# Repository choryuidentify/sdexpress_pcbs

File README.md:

# microSD Express PCBs

This repository contains several PCB designs for adapters related to microSD
Express cards.

- [M.2-M card to microSD Express socket](m2_m_card-to-usdex_socket/README.md)
- [microSD Express card to FPC](usdex_card-to-fpc/README.md)
- [fpc](fpc/README.md)
- [FPC to M.2-M socket](fpc-to-m2_m_socket/README.md)
- [microSD Express card to M.2-M socket](usdex-to-m2_m_socket/README.md)

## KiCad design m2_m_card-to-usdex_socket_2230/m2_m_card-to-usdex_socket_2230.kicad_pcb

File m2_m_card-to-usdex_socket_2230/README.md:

# M.2-M card to microSD Express socket

This allows connecting a microSD Express card directly to an M.2 Key M slot, so
you can use it as a PCIe NVME device.

See
[my blog post](https://mzimmermann.info/posts/a-microsd-express-card-in-an-m2-slot/)
for more information.

JLCPCB order parameters:

- **Gerber file**: gerbers_Y3
- **Build Time**: 5-6 days
- **Base Material**: FR-4
- **Layers**: 6
- **Dimension**: 22 mm * 80 mm
- **PCB Qty**: 5
- **Product Type**: Industrial/Consumer electronics
- **Different Design**: 1
- **Delivery Format**: Single PCB
- **PCB Thickness**: 0.8mm
- **Specify Stackup**: yes JLC06081H-2116
- **Impedance Control**: No requirement
- **PCB Color**: Green
- **Silkscreen**: White
- **Material Type**: FR-4 TG155
- **Via Covering**: Epoxy Filled & Capped
- **Surface Finish**: ENIG
- **Gold Fingers**: 2U"
- **Deburring/Edge rounding**: Yes
- **Outer Copper Weight**: 1 oz
- **Inner Copper Weight**: 0.5 oz
- **Gold Fingers**: Yes
- **Beveling**: No
- **Electrical Test**: Flying Probe Fully Test
- **Castellated Holes**: no
- **Press-Fit Hole**: No
- **Edge Plating**: No
- **Mark on PCB**: Remove Mark
- **Blind Slot**: No
- **Min via hole size/diameter**: 0.3mm/(0.4/0.45mm)
- **4-Wire Kelvin Test**: Yes
- **Paper between PCBs**: No
- **Appearance Quality**: IPC Class 2 Standard
- **Confirm Production file**: No
- **Silkscreen Technology**: Ink-jet/Screen Printing Silkscreen
- **Package Box**: With JLCPCB logo
- **Inspection Report**: No
- **Board Outline Tolerance**: ±0.2mm(Regular)

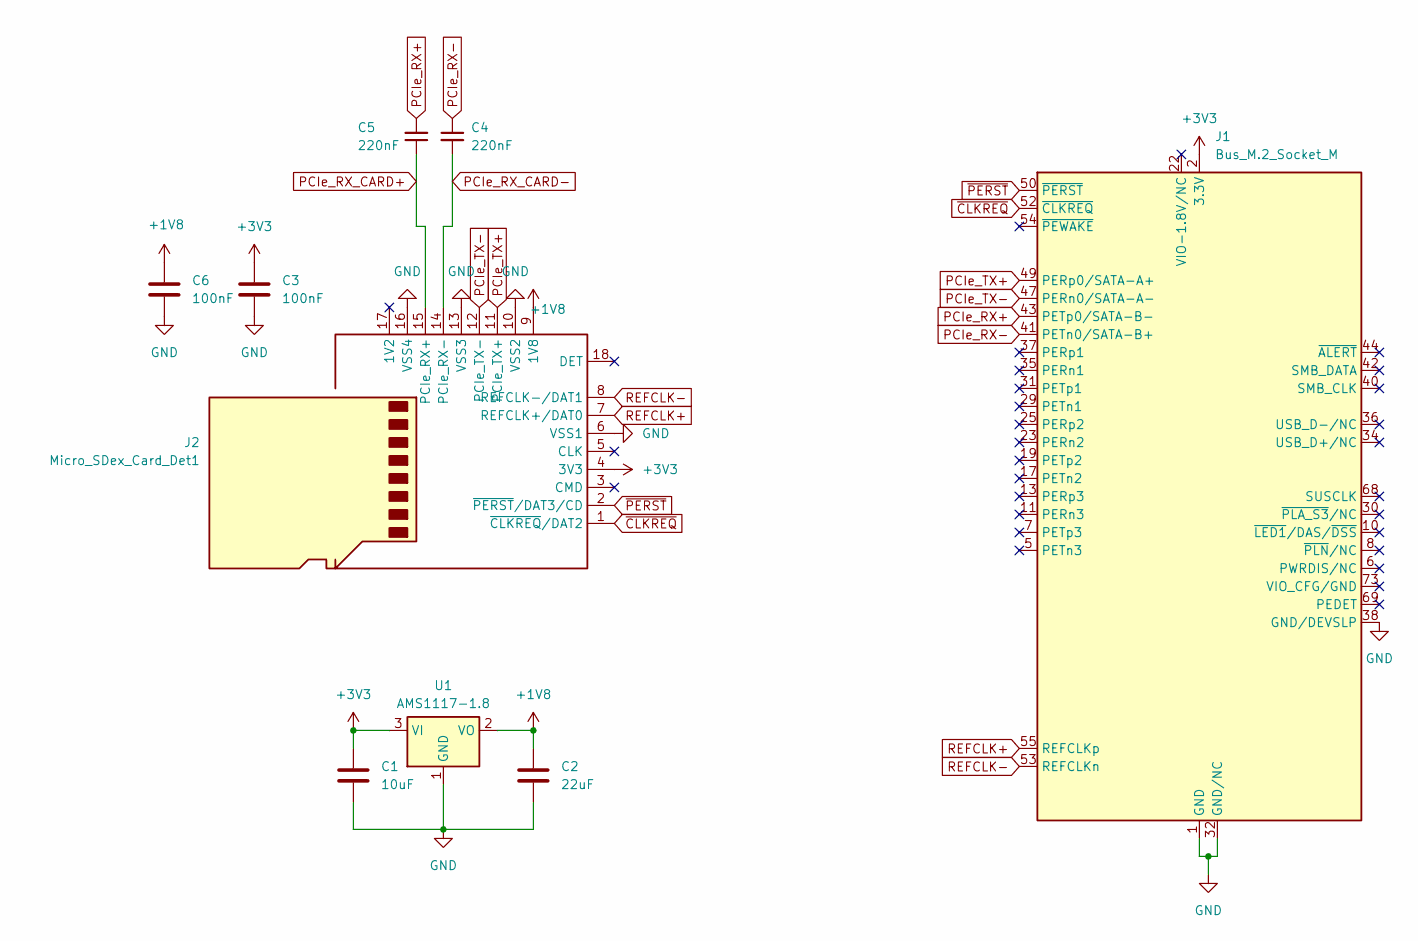
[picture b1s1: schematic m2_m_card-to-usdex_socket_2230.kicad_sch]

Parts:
C1: 10uF; C_0603_1608Metric
C2: 22uF; C_0603_1608Metric
C3, C6: 100nF; C_0603_1608Metric
C4, C5: 220nF; C_0603_1608Metric
J1: Bus_M.2_Socket_M; 2230-key-M
J2: Micro_SDex_Card_Det1; Amphenol 10102166A812A
U1: AMS1117-1.8; SOT-223-3_TabPin2

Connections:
+1V8: C2.1, C6.1, J2.9 (1V8), U1.2 (VO)
+3V3: C1.1, C3.1, J1.2 (3.3V), J1.4 (3.3V), J1.12 (3.3V), J1.14 (3.3V), J1.16 (3.3V), J1.18 (3.3V), J1.70 (3.3V), J1.72 (3.3V), J1.74 (3.3V), J2.4 (3V3), U1.3 (VI)
GND: C1.2, C2.2, C3.2, C6.2, J1.1 (GND), J1.3 (GND), J1.9 (GND), J1.15 (GND), J1.21 (GND), J1.27 (GND), J1.32 (GND/NC), J1.33 (GND), J1.38 (GND/DEVSLP), J1.39 (GND), J1.45 (GND), J1.51 (GND), J1.57 (GND), J1.71 (GND), J1.75 (GND), J1.76 (GND), J1.77 (GND), J2.6 (VSS1), J2.10 (VSS2), J2.13 (VSS3), J2.16 (VSS4), U1.1 (GND)
PCIe_RX+: C5.2, J1.43 (PETp0/SATA-B-)
PCIe_RX-: C4.1, J1.41 (PETn0/SATA-B+)
PCIe_RX_CARD+: C5.1, J2.15 (PCIe_RX+)
PCIe_RX_CARD-: C4.2, J2.14 (PCIe_RX-)
PCIe_TX+: J1.49 (PERp0/SATA-A+), J2.11 (PCIe_TX+)
PCIe_TX-: J1.47 (PERn0/SATA-A-), J2.12 (PCIe_TX-)
REFCLK+: J1.55 (REFCLKp), J2.7 (REFCLK+/DAT0)
REFCLK-: J1.53 (REFCLKn), J2.8 (REFCLK-/DAT1)
~CLKREQ: J1.52 (~CLKREQ), J2.1 (~CLKREQ/DAT2)
~PERST: J1.50 (~PERST), J2.2 (~PERST/DAT3/CD)

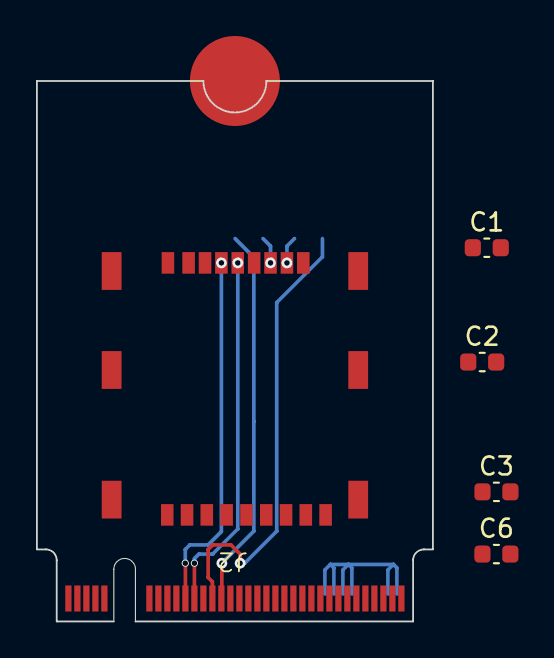
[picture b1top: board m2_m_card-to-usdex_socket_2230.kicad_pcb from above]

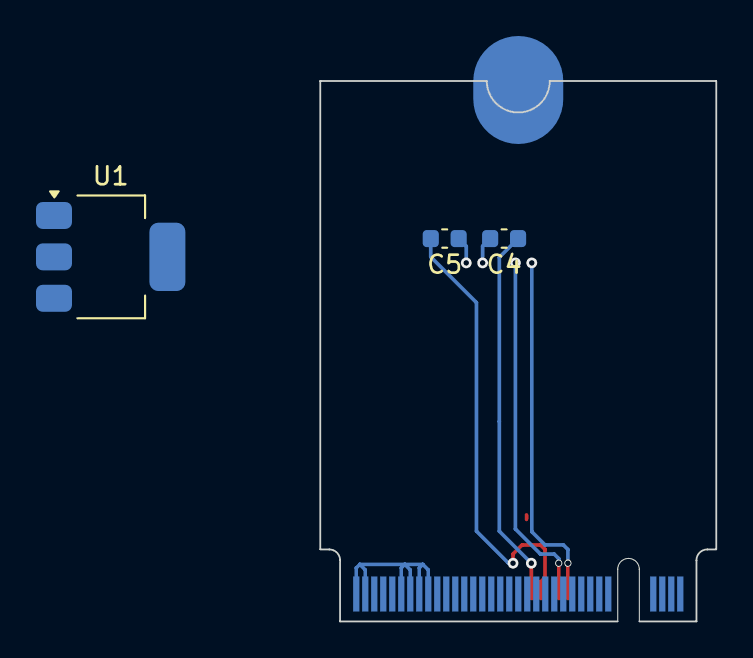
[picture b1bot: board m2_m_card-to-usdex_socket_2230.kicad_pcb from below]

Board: 2 copper layers, 22.0 x 30.0 mm, 9 parts (3 on the bottom side), 13 nets.

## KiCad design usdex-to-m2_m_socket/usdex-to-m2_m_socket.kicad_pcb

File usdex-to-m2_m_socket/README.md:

# microSD Express card to M.2-M socket

Connects an M.2 Key-M SSD to a microSD Express slot.

JLCPCB order parameters:

- **Gerber file**: usdex-to-m2_m_socket_Y8
- **Build Time**: 3-4 days (PCBA Only)
- **Base Material**: FR-4
- **Layers**: 6
- **Dimension**: 4 mm* 54.42 mm
- **PCB Qty**: 5
- **Product Type**: Industrial/Consumer electronics
- **Different Design**: 1
- **Delivery Format**: Single PCB
- **PCB Thickness**: 0.8mm
- **Specify Stackup**: yes JLC06081H-2116
- **Impedance Control**: No requirement
- **PCB Color**: Green
- **Silkscreen**: White
- **Material Type**: FR-4 TG155
- **Via Covering**: Epoxy Filled & Capped
- **Surface Finish**: ENIG Gold Fingers: 2U"
- **Deburring/Edge rounding**: No
- **Outer Copper Weight**: 1 oz
- **Inner Copper Weight**: 0.5 oz
- **Gold Fingers**: Yes
- **Electrical Test**: Flying Probe Fully Test
- **Castellated Holes**: no
- **Press-Fit Hole**: No
- **Edge Plating**: No
- **Mark on PCB**: Remove Mark
- **Blind Slot**: No
- **Min via hole size/diameter**: 0.3mm/(0.4/0.45mm)
- **4-Wire Kelvin Test**: No
- **Paper between PCBs**: No
- **Appearance Quality**: IPC Class 2* Standard
- **Confirm Production file**: No
- **Silkscreen Technology**: Ink-jet/Screen Printing Silkscreen
- **Package Box**: With JLCPCB logo
- **Inspection Report**: No
- **Board Outline Tolerance**: ±0.2mm(Regular)

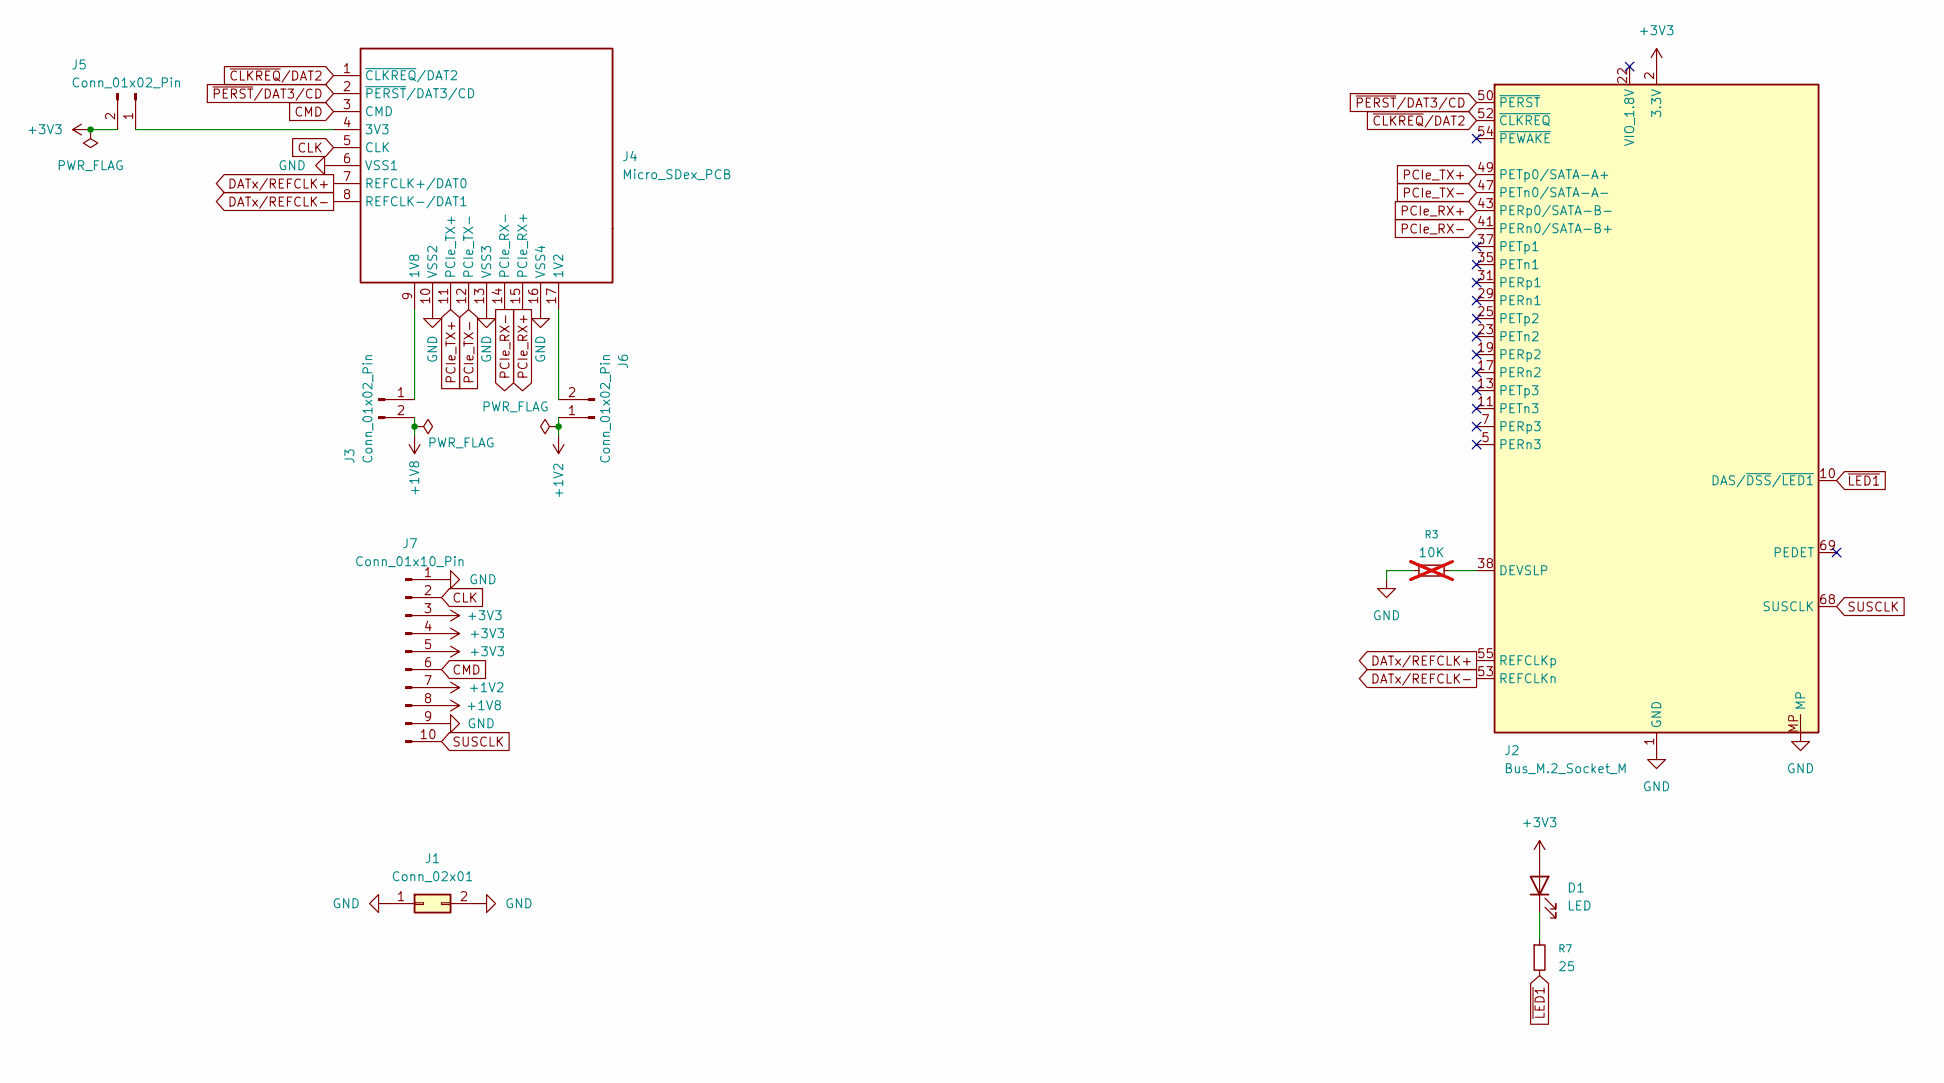
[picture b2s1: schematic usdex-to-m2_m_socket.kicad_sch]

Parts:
D1: LED; LED_0805_2012Metric; LCSC Part # C2297
J1: Conn_02x01; PinHeader_1x02_P2.54mm_Vertical
J2: Bus_M.2_Socket_M; CONN-SMD_APCI0146-P001A-nohole; LCSC Part # C841645
J3, J5, J6: Conn_01x02_Pin; PinHeader_1x02_P2.54mm_Vertical
J4: Micro_SDex_PCB; usdex-male-open_bottom
J7: Conn_01x10_Pin; PinHeader_1x10_P2.54mm_Vertical
R3: 10K; R_0402_1005Metric; not fitted
R7: 25; R_0805_2012Metric; LCSC Part # C17544

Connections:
+1V2: J6.1, J7.7
+1V8: J3.2, J7.8
+3V3: D1.2 (A), J2.2 (3.3V), J2.4 (3.3V), J2.12 (3.3V), J2.14 (3.3V), J2.16 (3.3V), J2.18 (3.3V), J2.70 (3.3V), J2.72 (3.3V), J2.74 (3.3V), J5.2, J7.3, J7.4, J7.5
CLK: J4.5 (CLK), J7.2
CMD: J4.3 (CMD), J7.6
DATx/REFCLK+: J2.55 (REFCLKp), J4.7 (REFCLK+/DAT0)
DATx/REFCLK-: J2.53 (REFCLKn), J4.8 (REFCLK-/DAT1)
GND: J1.1, J1.2, J2.1 (GND), J2.3 (GND), J2.9 (GND), J2.15 (GND), J2.21 (GND), J2.27 (GND), J2.33 (GND), J2.39 (GND), J2.45 (GND), J2.51 (GND), J2.57 (GND), J2.71 (GND), J2.73 (GND), J2.75 (GND), J2.MP, J4.6 (VSS1), J4.10 (VSS2), J4.13 (VSS3), J4.16 (VSS4), J7.1, J7.9, R3.1
unnamed: D1.1 (K), R7.1
unnamed: J2.38 (DEVSLP), R3.2
unnamed: J3.1, J4.9 (1V8)
unnamed: J4.17 (1V2), J6.2
unnamed: J4.4 (3V3), J5.1
PCIe_RX+: J2.43 (PERp0/SATA-B-), J4.15 (PCIe_RX+)
PCIe_RX-: J2.41 (PERn0/SATA-B+), J4.14 (PCIe_RX-)
PCIe_TX+: J2.49 (PETp0/SATA-A+), J4.11 (PCIe_TX+)
PCIe_TX-: J2.47 (PETn0/SATA-A-), J4.12 (PCIe_TX-)
SUSCLK: J2.68 (SUSCLK), J7.10
~CLKREQ/DAT2: J2.52 (~CLKREQ), J4.1 (~CLKREQ/DAT2)
~LED1: J2.10 (DAS/~DSS/~LED1), R7.2
~PERST/DAT3/CD: J2.50 (~PERST), J4.2 (~PERST/DAT3/CD)

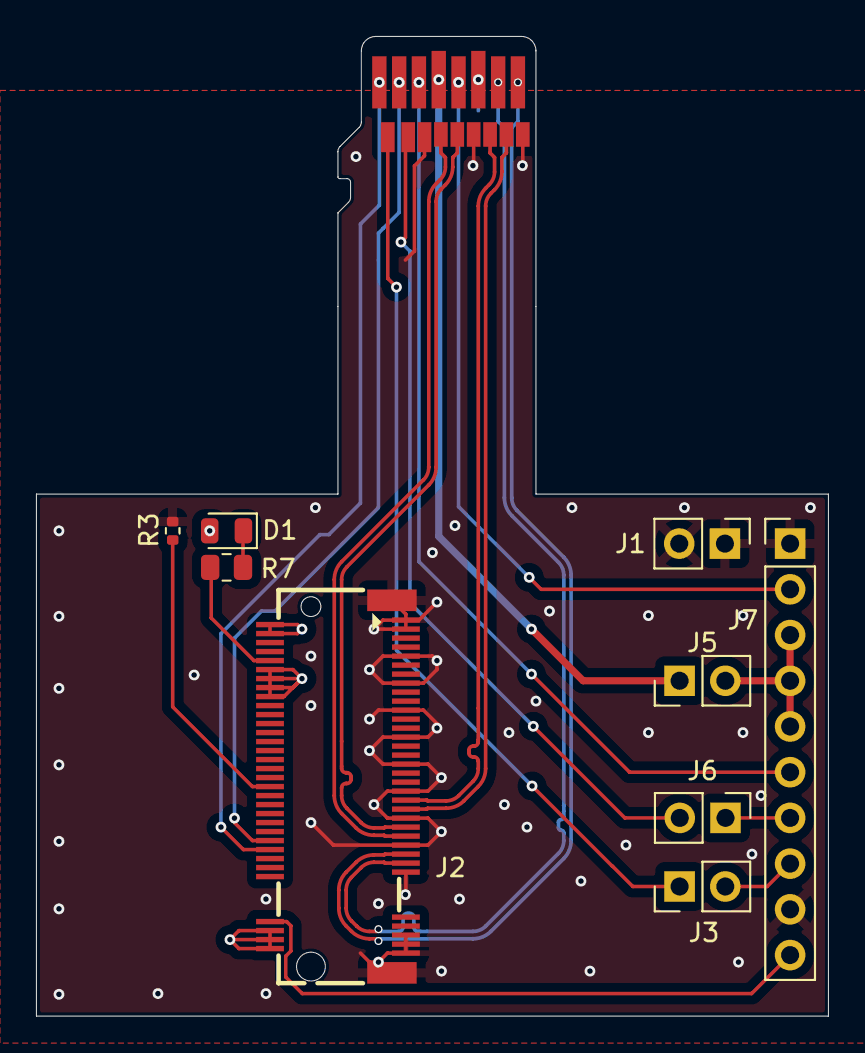
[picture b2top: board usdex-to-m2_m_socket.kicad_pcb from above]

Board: 6 copper layers, 44.0 x 54.4 mm, 10 parts (0 on the bottom side), 21 nets.

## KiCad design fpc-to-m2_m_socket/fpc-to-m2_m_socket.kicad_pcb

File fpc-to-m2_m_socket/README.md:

# FPC to M.2-M socket

> [!WARNING]
> This didn't work out due issues with properly soldering the FPC.

Connects an M.2 Key-M SSD to [FPC](../fpc/README.md).

JLCPCB order parameters:

- **Gerber file**: fpc-to-m2_m_socket_Y4
- **Build Time**: 3-4 days (PCBA Only)
- **Base Material**: FR-4
- **Layers**: 6
- **Dimension**: 99.3 mm* 70.58 mm
- **PCB Qty**: 5
- **Product Type**: Industrial/Consumer electronics
- **Different Design**: 1
- **Delivery Format**: Single PCB
- **PCB Thickness**: 0.8mm
- **Specify Stackup**: yes JLC06081H-2116
- **Impedance Control**: No requirement
- **PCB Color**: Green
- **Silkscreen**: White
- **Material Type**: FR-4 TG155
- **Via Covering**: Epoxy Filled & Capped
- **Surface Finish**: ENIG Gold Fingers: 2U"
- **Deburring/Edge rounding**: No
- **Outer Copper Weight**: 1 oz
- **Inner Copper Weight**: 0.5 oz
- **Gold Fingers**: No
- **Electrical Test**: Flying Probe Fully Test
- **Castellated Holes**: no
- **Press-Fit Hole**: No
- **Edge Plating**: No
- **Mark on PCB**: Remove Mark
- **Blind Slot**: No
- **Min via hole size/diameter**: 0.3mm/(0.4/0.45mm)
- **4-Wire Kelvin Test**: No
- **Paper between PCBs**: No
- **Appearance Quality**: IPC Class 2* Standard
- **Confirm Production file**: Yes
- **Silkscreen Technology**: Ink-jet/Screen Printing Silkscreen
- **Package Box**: With JLCPCB logo
- **Inspection Report**: No
- **Board Outline Tolerance**: ±0.2mm(Regular)

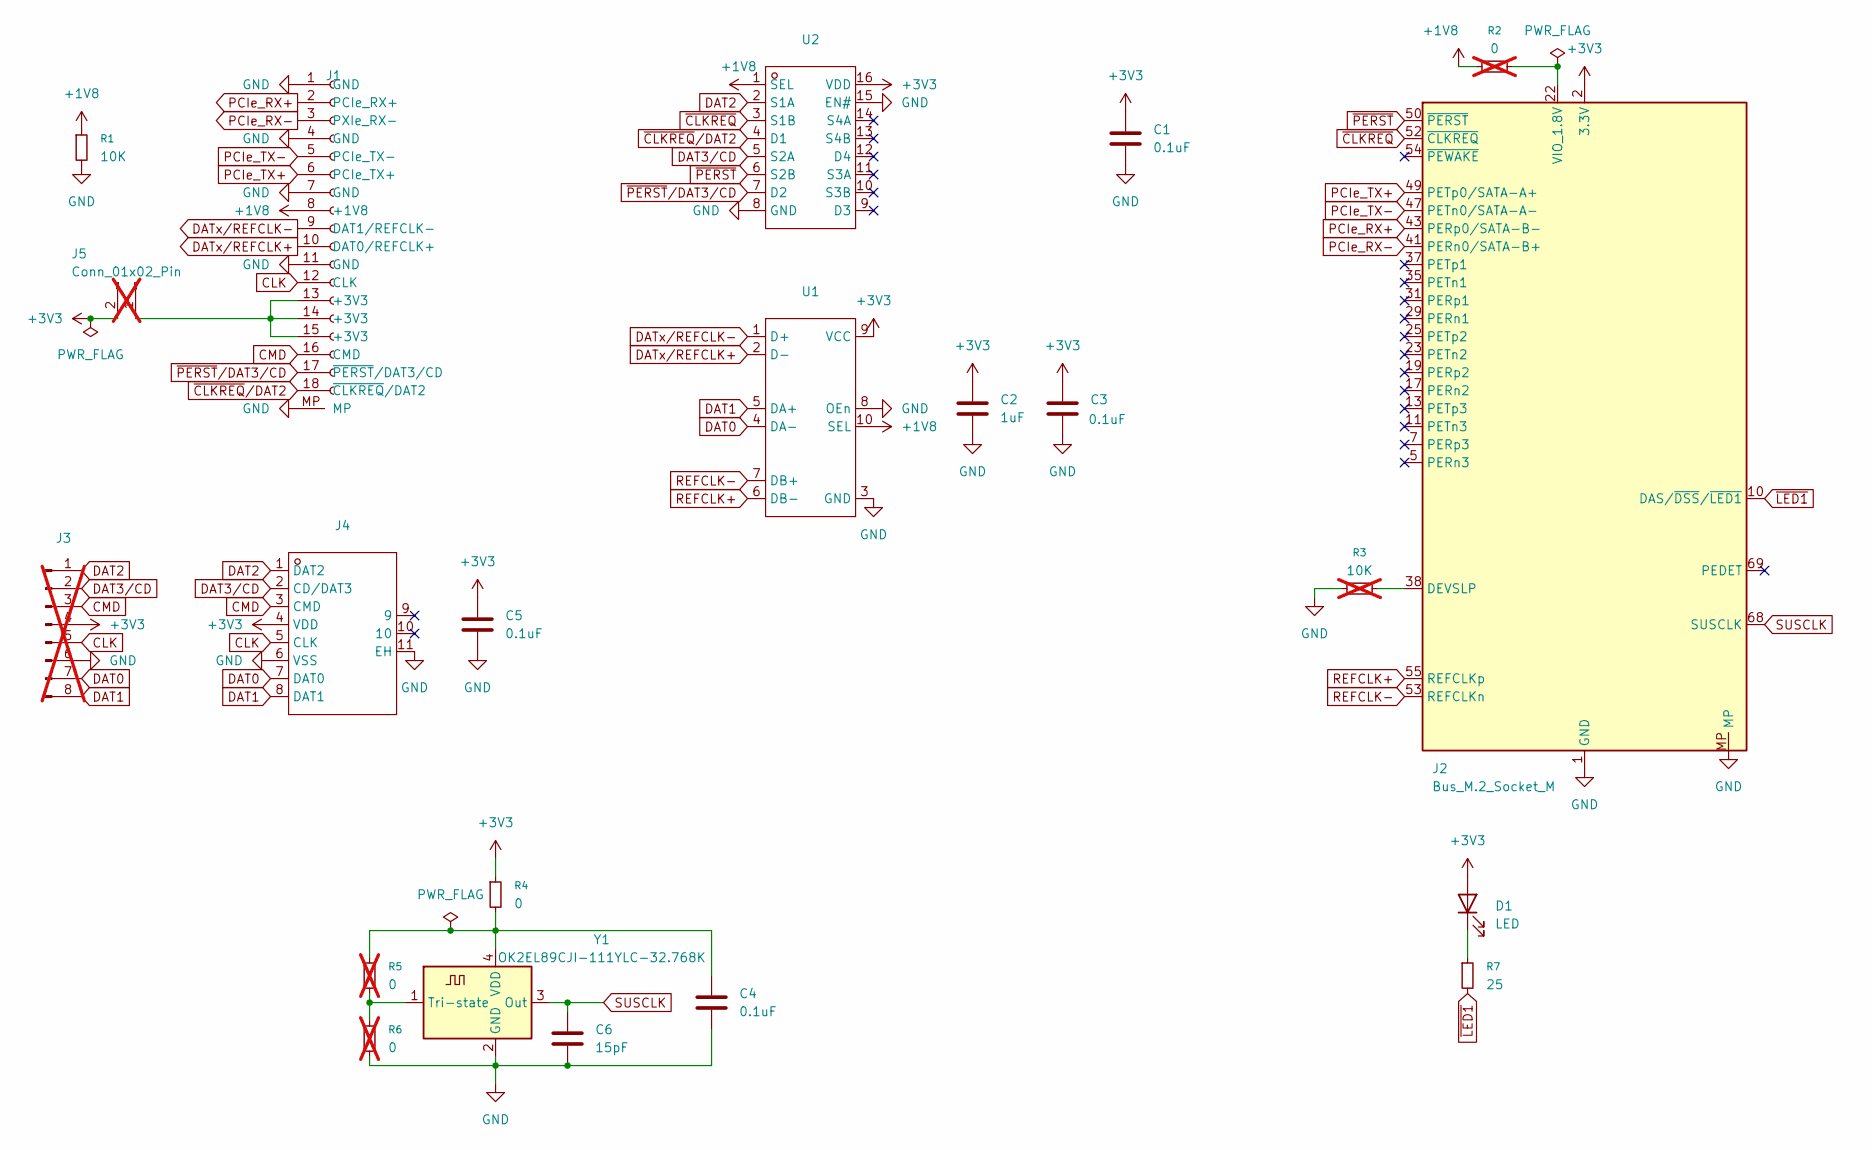
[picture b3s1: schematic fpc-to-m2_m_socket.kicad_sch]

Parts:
C1, C3, C4, C5: 0.1uF; C_0402_1005Metric; LCSC Part # C1525
C2: 1uF; C_0402_1005Metric; LCSC Part # C52923
C6: 15pF; C_0402_1005Metric; LCSC Part # C1548
D1: LED; LED_0805_2012Metric; LCSC Part # C2297
J1: FPC-SMD_18P-P1.00_JS_AFA07-S18XXX; LCSC Part # C262744
J2: Bus_M.2_Socket_M; CONN-SMD_APCI0146-P001A; LCSC Part # C841645
J3: PinHeader_1x08_P2.54mm_Vertical; not fitted
J4: TF-SMD_503398-1892; Manufacturer Part 5033981892; LCSC Part Name 自弹式 MicroSD卡(TF卡) 卡座
J5: Conn_01x02_Pin; PinHeader_1x02_P2.54mm_Vertical; not fitted
R1: 10K; R_0402_1005Metric; LCSC Part # C25744
R2, R5, R6: 0; R_0402_1005Metric; not fitted
R3: 10K; R_0402_1005Metric; not fitted
R4: 0; R_0402_1005Metric; LCSC Part # C17168
R7: 25; R_0805_2012Metric; LCSC Part # C17544
U1: TMUXHS221NKGT; Manufacturer Part TMUXHS221NKGT; LCSC Part Name TMUXHS221 USB 2.0 480Mbps 2:1/1:2 多路复用器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
U2: TSSOP-16_4.4x5mm_P0.65mm; Manufacturer Part TMUX1574PWR; LCSC Part Name TMUX1574低电容、2:1(SPDT)4通道断电保护开关
Y1: OK2EL89CJI-111YLC-32.768K; OSC-SMD_4P-L3.2-W2.5-BL_TG-5006CE; LCSC Part # C5280579

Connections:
+1V8: J1.8 (+1V8), R1.1, R2.1, U1.10 (SEL), U2.1 (SEL)
+3V3: C1.1, C2.1, C3.1, C5.1, D1.2 (A), J2.2 (3.3V), J2.4 (3.3V), J2.12 (3.3V), J2.14 (3.3V), J2.16 (3.3V), J2.18 (3.3V), J2.70 (3.3V), J2.72 (3.3V), J2.74 (3.3V), J3.4, J4.4 (VDD), J5.2, R4.1, U1.9 (VCC), U2.16 (VDD)
CLK: J1.12 (CLK), J3.5, J4.5 (CLK)
CMD: J1.16 (CMD), J3.3, J4.3 (CMD)
DAT0: J3.7, J4.7 (DAT0), U1.4 (DA-)
DAT1: J3.8, J4.8 (DAT1), U1.5 (DA+)
DAT2: J3.1, J4.1 (DAT2), U2.2 (S1A)
DAT3/CD: J3.2, J4.2 (CD/DAT3), U2.5 (S2A)
DATx/REFCLK+: J1.10 (DAT0/REFCLK+), U1.2 (D-)
DATx/REFCLK-: J1.9 (DAT1/REFCLK-), U1.1 (D+)
GND: C1.2, C2.2, C3.2, C4.2, C5.2, C6.2, J1.1 (GND), J1.4 (GND), J1.7 (GND), J1.11 (GND), J1.MP, J2.1 (GND), J2.3 (GND), J2.9 (GND), J2.15 (GND), J2.21 (GND), J2.27 (GND), J2.33 (GND), J2.39 (GND), J2.45 (GND), J2.51 (GND), J2.57 (GND), J2.71 (GND), J2.73 (GND), J2.75 (GND), J2.MP, J3.6, J4.6 (VSS), J4.11 (EH), R1.2, R3.1, R6.1, U1.3 (GND), U1.8 (OEn), U2.8 (GND), U2.15 (EN#), Y1.2 (GND)
unnamed: D1.1 (K), R7.1
unnamed: J2.38 (DEVSLP), R3.2
unnamed: J2.22 (VIO_1.8V), R2.2
unnamed: J1.13 (+3V3), J1.14 (+3V3), J1.15 (+3V3), J5.1
unnamed: R5.1, R6.2, Y1.1 (Tri-state)
unnamed: C4.1, R4.2, R5.2, Y1.4 (VDD)
PCIe_RX+: J1.2 (PCIe_RX+), J2.43 (PERp0/SATA-B-)
PCIe_RX-: J1.3 (PXIe_RX-), J2.41 (PERn0/SATA-B+)
PCIe_TX+: J1.6 (PCIe_TX+), J2.49 (PETp0/SATA-A+)
PCIe_TX-: J1.5 (PCIe_TX-), J2.47 (PETn0/SATA-A-)
REFCLK+: J2.55 (REFCLKp), U1.6 (DB-)
REFCLK-: J2.53 (REFCLKn), U1.7 (DB+)
SUSCLK: C6.1, J2.68 (SUSCLK), Y1.3 (Out)
~CLKREQ: J2.52 (~CLKREQ), U2.3 (S1B)
~CLKREQ/DAT2: J1.18 (~CLKREQ/DAT2), U2.4 (D1)
~LED1: J2.10 (DAS/~DSS/~LED1), R7.2
~PERST: J2.50 (~PERST), U2.6 (S2B)
~PERST/DAT3/CD: J1.17 (~PERST/DAT3/CD), U2.7 (D2)

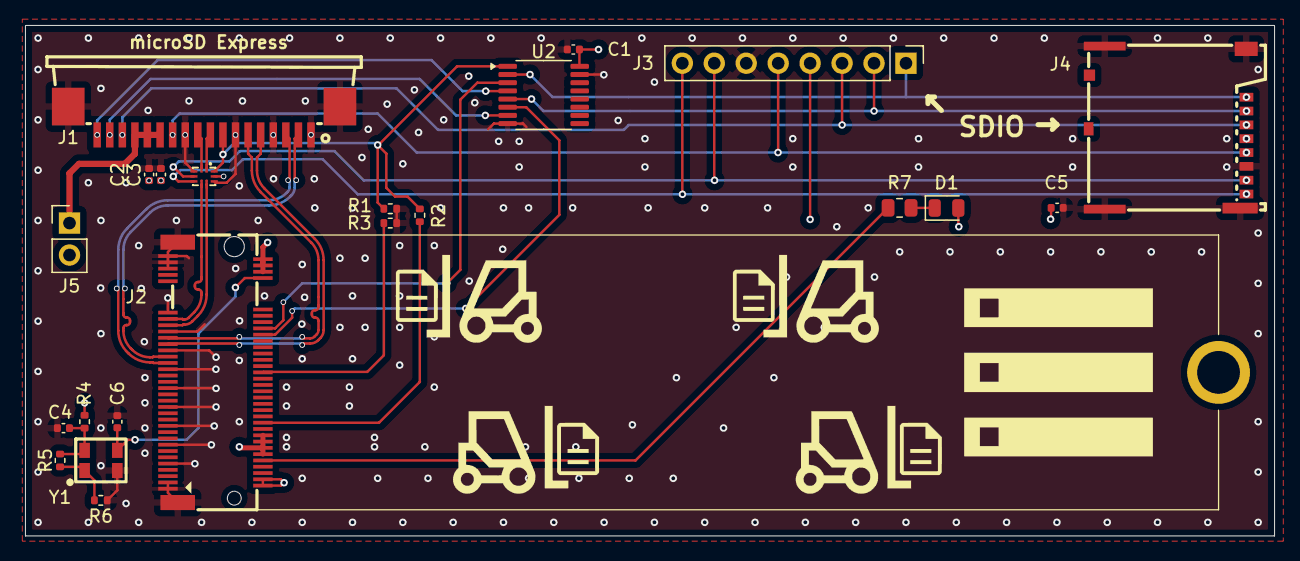
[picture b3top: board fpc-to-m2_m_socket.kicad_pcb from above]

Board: 6 copper layers, 99.3 x 40.6 mm, 22 parts (0 on the bottom side), 29 nets.

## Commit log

2025-04-12 add adryzz's m.2 footprints
2025-04-12 add gitignore
    Source: https://raw.githubusercontent.com/github/gitignore/refs/heads/main/KiCad.gitignore
2025-04-12 add empty m2-e-usdex project
2025-04-12 add 2230 key-E m.2 connector
    Source: https://github.com/adryzz/M.2-Key-E-Footprints/blob/1b8806e49a4fc1739f1da2d519d7594bfc169386/2230-key-E.kicad_mod
2025-04-12 2230-e: use 2.5mm height pins for back side
2025-04-12 2230-e: move center of card to center
    This makes it easier to compare with the spec.
2025-04-12 2230-e: correct key location
2025-04-12 create 2280-m
    This is just a copy of 2230-e for now
2025-04-12 2280-m: resize from 30 to 80
2025-04-12 2280-m: move key
2025-04-29 m2-e-usdex: Initial m2 m key usdex design
    This is actually M key instead of e key now. I'll rename it later.
    This is almost done and just needs some final touches.
2025-04-29 m2-e-usdex: add testpoint and fill planes
2025-04-29 m2-e-usdex: Create fillets
    I did this in a separate commit, because this can't be undone and
    creating the free angle differential lines was a very long, painful and
    manual process.
2025-04-29 m2-e-usdex: add gerbers
    This is what I actually produced
2025-04-29 move m2-e-usdex/m2-e-usdex to m2-e-usdex
    I did not expect kicad to create a directory by itself.
2025-04-29 rename m2-e-usdex to m2-m-usdex
2025-04-29 m2-m-usdex: remove gerbers
    They don't really reflect the project anymore after all these renames
    and they are still available on the 1.0.0 tag anyway.
2025-04-29 Revert "add adryzz's m.2 footprints"
    This reverts commit 83ab88f8506a513fff1dd20d7b216de3c5643a9b.
    I didn't end up using it directly because I had to make major changes. I
    have a copy in my personal library in this repo.
2025-04-29 add 3d model source list
2025-05-03 m2-m-usdex: Rename to m2_m_card-to-usdex_socket
    That seems much clearer given that I'm about to create an
    m2_m_socket-to-usdex_card adapter.
2025-05-14 Add usdex-card to m2-m-socket adapter
    this consists of 3 designs:
    - a usdex card
    - a flex PCB
    - the main board with the m.2 socket
2025-05-14 m2_m_card-to-usdex_socket: Add impedance information
2025-05-14 add fillets and skew tuning
2025-05-14 fpc-to-m2_m_socket: switch TMUX1574 to TSSOP-16
    The UQFN-16 variant just went out of stock at jlcpcb.
2025-05-14 add production files
2025-05-16 Add READMEs
2025-06-11 usdex-to-m2_m_socket: tune skew
2025-06-11 usdex-to-m2_m_socket: fillet tracks
2025-06-11 add usdex-to-m2_m_socket
2025-06-11 usdex-to-m2_m_socket: move GND vias
2025-06-11 usdex-to-m2_m_socket: add production files
2025-10-01 m2_m_card-to-usdex_socket: adjust via holes and smd size
    for reduce production cost!
2025-10-01 m2_m_card-to-usdex_socket: Update README.md
2025-10-12 2230 variant: initial commit
